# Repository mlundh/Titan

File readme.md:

# Titan

Development board for robotics, drones and misc. projects. Initially designed to support [QuadSys](https://github.com/mlundh/QuadSys) development.

## Getting Started

These instructions will get you a copy of the project up and running on your local machine for development.

### Prerequisites

Install [KiCad](https://kicad-pcb.org/download/)

Example KiCad 5.1 for ubuntu:
```
sudo add-apt-repository --yes ppa:js-reynaud/kicad-5.1
sudo apt update
sudo apt install --install-recommends kicad
# If you want demo projects
sudo apt install kicad-demo
```
## Versioning

Each version I have manufactured is listed as a tag with only a version number in the repository.

Example:
```
v1.0
```
Each version that has been manufactured and verified will get tagged with vesion number and "_verified".

Example (does at time of writing this not exist):
```
v1.0_verified
```

## Authors

* **Martin Lundh** - [mlundh](https://github.com/mlundh)

## License

This project is licensed under the MIT License - see the [LICENSE.md](LICENSE.md) file for details

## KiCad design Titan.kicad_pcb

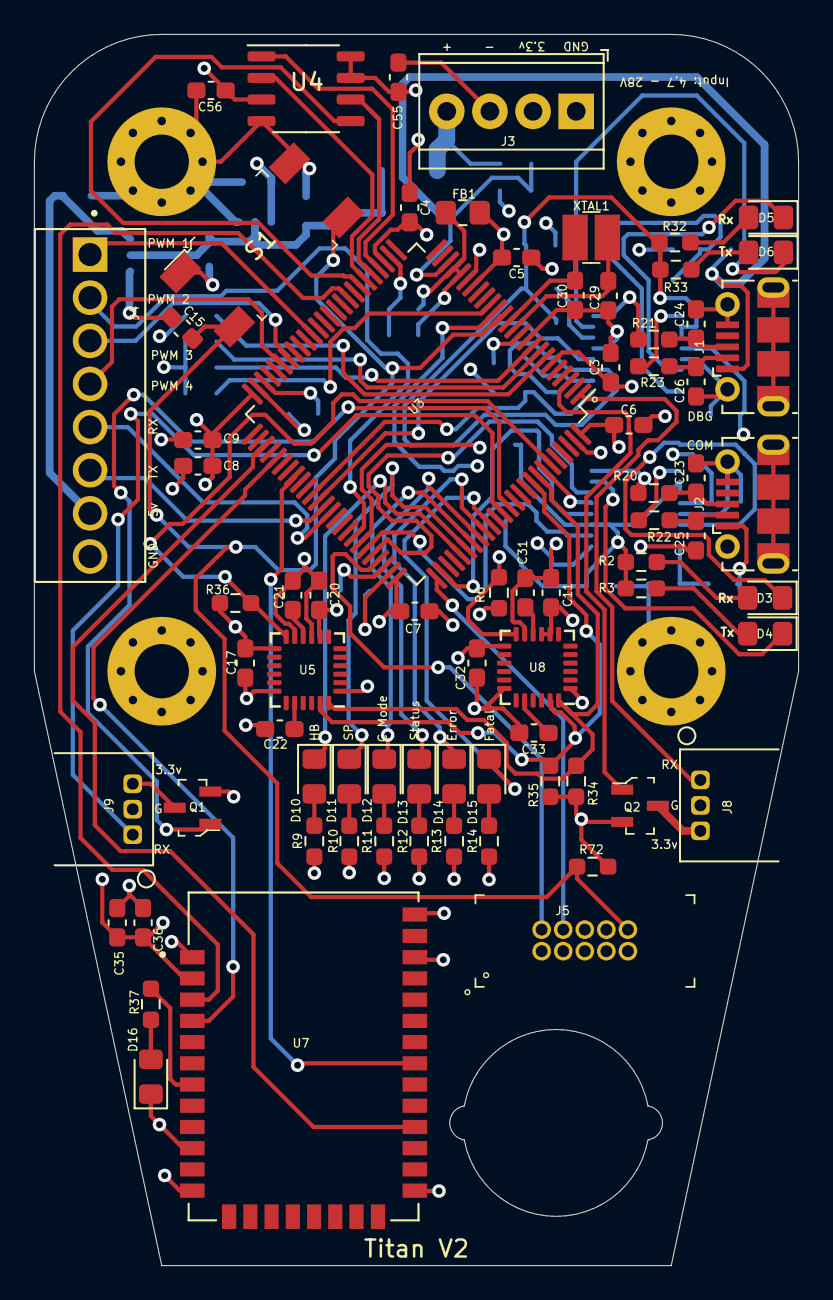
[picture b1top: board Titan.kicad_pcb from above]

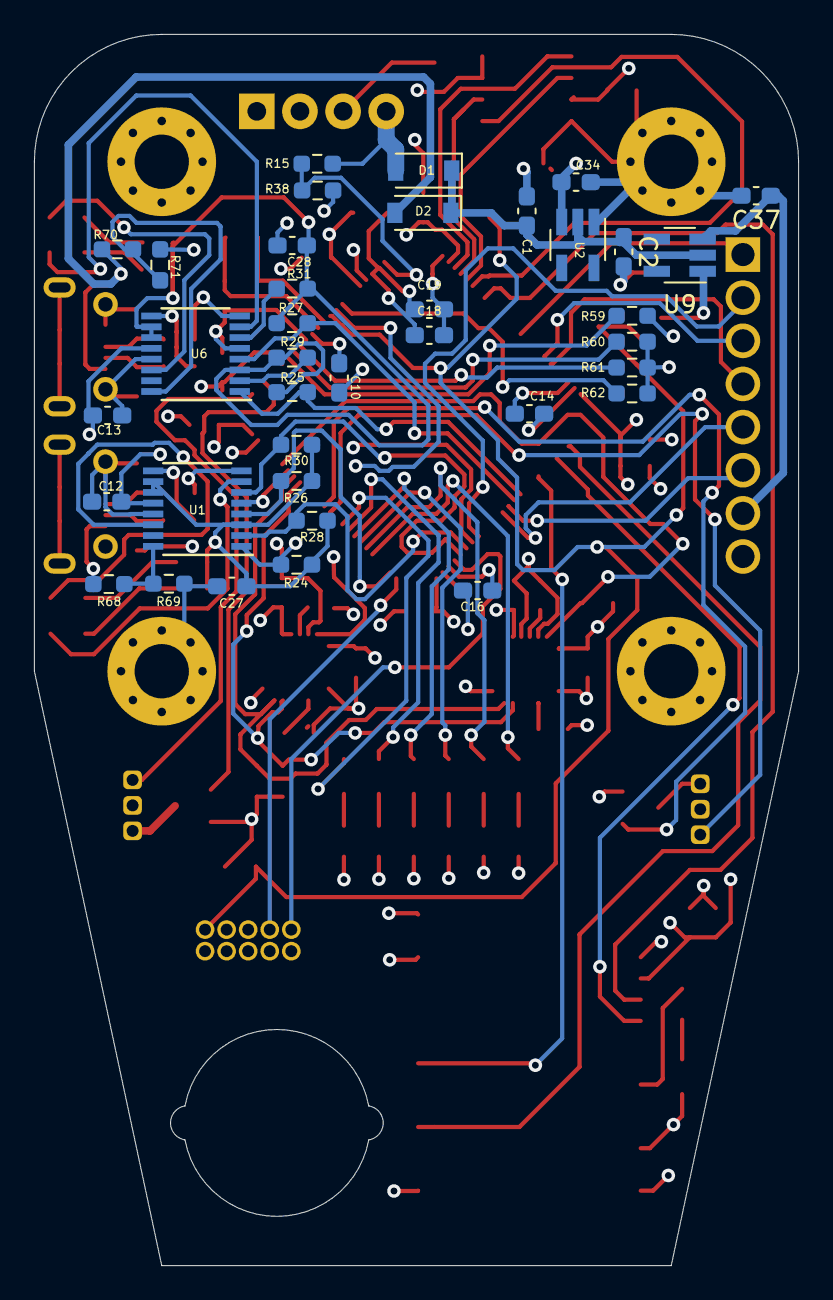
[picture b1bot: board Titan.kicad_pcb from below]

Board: 4 copper layers, 45.0 x 72.5 mm, 115 parts (37 on the bottom side), 90 nets.

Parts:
C1, C2, C14, C16, C22, C33, C34, C37: 2.2uF; C_0603_1608Metric_Pad1.08x0.95mm_HandSolder
C3, C4, C5, C6, C7, C8, C9, C12, C13, C15, C18, C27, C28: 100nF; C_0603_1608Metric_Pad1.08x0.95mm_HandSolder
C10: 10uF; C_0603_1608Metric_Pad1.08x0.95mm_HandSolder
C11, C20, C21, C31, C55: 0.1uF; C_0603_1608Metric_Pad1.08x0.95mm_HandSolder
C17, C32, C56: 10nF; C_0603_1608Metric_Pad1.08x0.95mm_HandSolder
C19, C35: 1uF; C_0603_1608Metric_Pad1.08x0.95mm_HandSolder
C23, C24, C25, C26: 47pF; C_0603_1608Metric_Pad1.08x0.95mm_HandSolder
C29, C30, C36: 8.2pF; C_0603_1608Metric_Pad1.08x0.95mm_HandSolder
D1, D2: D_Schottky; D_SOD-123
D3, D5: RXLED; LED_0805_2012Metric_Pad1.15x1.40mm_HandSolder
D4, D6: TXLED; LED_0805_2012Metric_Pad1.15x1.40mm_HandSolder
D10: LED_Heartbeat; LED_0805_2012Metric_Pad1.15x1.40mm_HandSolder
D11: LED_Valid_SP; LED_0805_2012Metric_Pad1.15x1.40mm_HandSolder
D12: LED_Status; LED_0805_2012Metric_Pad1.15x1.40mm_HandSolder
D13: LED_Mode; LED_0805_2012Metric_Pad1.15x1.40mm_HandSolder
D14: LED_Error_Log; LED_0805_2012Metric_Pad1.15x1.40mm_HandSolder
D15: LED_Fatal_Error; LED_0805_2012Metric_Pad1.15x1.40mm_HandSolder
D16: LED; LED_0805_2012Metric_Pad1.15x1.40mm_HandSolder
FB1: Ferrite_Bead; R_0805_2012Metric_Pad1.20x1.40mm_HandSolder
H1, H2, H3, H4: MountingHole_Pad; MountingHole_3.2mm_M3_Pad_Via
J1, J2: USB_B_Micro; USB_Micro-B_Molex-105017-0001
J3: PWR CON; TerminalBlock_TE_282834-4_1x04_P2.54mm_Horizontal
J4: Screw_Terminal_01x08; HDRV8W85P254_8X1_2078X650X1000
J5: Debug; PinHeader_2x5_P1.27mm_Drill.7mm
J8, J9: S3B-ZR(LF)(SN)
Q1, Q2: NDS332P; SOT-23-3
R2, R3, R9, R10, R11, R12, R13, R14, R32, R33, R37: 330; R_0603_1608Metric_Pad0.98x0.95mm_HandSolder
R6, R36: 47k; R_0603_1608Metric_Pad0.98x0.95mm_HandSolder
R15: 100k; R_0603_1608Metric_Pad0.98x0.95mm_HandSolder
R20, R21, R22, R23: 27; R_0603_1608Metric_Pad0.98x0.95mm_HandSolder
R24, R25, R26, R27, R28, R29, R30, R31, R59, R60, R61, R62, R69, R71, R72: 10k; R_0603_1608Metric_Pad0.98x0.95mm_HandSolder
R34, R35: 4.7k; R_0603_1608Metric_Pad0.98x0.95mm_HandSolder
R38: 20k; R_0603_1608Metric_Pad0.98x0.95mm_HandSolder
R68, R70: 4,7k; R_0603_1608Metric_Pad0.98x0.95mm_HandSolder
S1: Reset button; Switch_Tactile_SMD_6x6mm
U1, U6: FT230XS; SSOP-16_3.9x4.9mm_P0.635mm
U2: ST732M33R; SOT-23-5_HandSoldering
U3: STM32F413VGTx; LQFP-100_14x14mm_P0.5mm
U4: CY15B104Q; SOP-8_3.9x4.9mm_P1.27mm
U5, U8: MPU-6050; InvenSense_QFN-24_4x4mm_P0.5mm
U7: XBEE3Micro; XCVR_XB3-24Z8UM-J
U9: ST732M50R; SOT-23-5_HandSoldering
XTAL1: NX3225GD-8MHZ-STD-CRA-3; SMD-2_3.2x2.5mm

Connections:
+5V: C37.1, J4.7, U9.3
/ADC_BAT: R15.1, R38.2, U3.23
/I2C_SCL_IMU: R35.2, U3.92, U5.23, U8.23
/I2C_SDA_IMU: R34.2, U3.93, U5.24, U8.24
/IMU1_INT: R36.1, U3.95, U5.12
/IMU2_INT: R6.1, U3.15, U8.12
/LED_CTRL_MODE: D12.1, U3.82
/LED_ERROR: D14.1, U3.84
/LED_FATAL: D15.1, U3.85
/LED_HEARTBEAT: D10.1, U3.80
/LED_SETPOINT: D11.1, U3.81
/LED_STATUS: D13.1, U3.83
/PWM_1: J4.1, U3.40
/PWM_2: J4.2, U3.68
/PWM_3: J4.3, U3.44
/PWM_4: J4.4, U3.45
/RC_1_PWR_CTRL: Q2.1, U3.3
/RC_2_PWR_CTRL: Q1.1, U3.88
/REV1: R59.2, U3.7
/REV2: R60.2, U3.8
/REV3: R61.2, U3.9
/REV4: R62.2, U3.16
/SPI_MEM_MISO: U3.31, U4.2
/SPI_MEM_MOSI: U3.32, U4.5
/SPI_MEM_NSS: U3.29, U4.1
/SPI_MEM_SCK: U3.30, U4.6
/SWCLK: J5.4, U3.76
/SWDIO: J5.2, U3.72
/UART_COM_CTS: U3.58, U7.27
/UART_COM_RTS: U3.53, U7.24
/UART_COM_RX: U3.34, U7.3
/UART_COM_TX: U3.55, U7.4
/UART_COM_USB_CTS: R28.2, U1.2, U3.70
/UART_COM_USB_RTS: R30.2, U1.6, U3.71
/UART_COM_USB_RX: R24.2, U1.1, U3.69
/UART_COM_USB_TX: R26.2, U1.4, U3.77
/UART_DBG_RX: R25.2, U3.61, U6.1
/UART_DBG_TX: R27.2, U3.62, U6.4
/UART_MOTOR_2_RX: J4.5, U3.64
/UART_MOTOR_2_TX: J4.6, U3.63
/UART_RC_1_RX: J8.3, U3.1
/UART_RC_2_RX: J9.3, U3.87
/VBUS_COM: D2.2, J1.1, R70.1
/nRESET: C15.1, J5.10, R72.2, S1.3, S1.4, U3.14
GND: C1.2, C2.2, C3.2, C4.2, C5.2, C6.2, C7.2, C8.2, C9.2, C10.2, C11.1, C12.1, C13.1, C14.2, C15.2, C16.2, C17.1, C18.2, C19.2, C20.1, C21.2, C22.2, C23.2, C24.2, C25.2, C26.2, C27.1, C28.1, C29.2, C30.2, C31.2, C32.1, C33.2, C34.2, C35.2, C36.1, C37.2, C55.1, C56.1, D16.1, H1.1, H2.1, H3.1, H4.1, J1.5, J1.6, J2.5, J2.6, J3.1, J3.3, J4.8, J5.3, J5.5, J5.9, J8.2, J9.2, R38.1, R60.1, R61.1, R62.1, R69.2, R71.2, S1.1, S1.2, U1.5, U1.13, U2.1, U3.10, U3.20, U3.27, U3.49, U3.74, U3.94, U3.99, U4.4, U5.1, U5.9, U5.11, U5.18, U6.5, U6.13, U7.1, U7.10, U7.12, U7.21, U7.32, U7.34, U8.1, U8.11, U8.18, U9.1
unnamed: C1.1, C2.1, D1.1, D2.1, U2.2, U9.2
unnamed: C14.1, U3.48
unnamed: C16.1, U3.73
unnamed: C21.1, U5.10
unnamed: C22.1, U5.20
unnamed: C23.1, J2.3, R20.2
unnamed: C24.1, J1.3, R21.2
unnamed: C25.1, J2.2, R22.2
unnamed: C26.1, J1.2, R23.2
unnamed: C27.2, R2.1, R3.1, R24.1, R26.1, R28.1, R30.1, U1.3, U1.10, U1.11
unnamed: C28.2, R25.1, R27.1, R29.1, R31.1, R32.1, R33.1, U6.3, U6.10, U6.11
unnamed: C29.1, U3.12, XTAL1.1
unnamed: C30.1, U3.13, XTAL1.2
unnamed: C31.1, U8.10
unnamed: C33.1, U8.20
unnamed: D1.2, J3.4, R15.2
unnamed: D3.1, U1.14
unnamed: D3.2, R2.2
unnamed: D4.1, U1.7
unnamed: D4.2, R3.2
unnamed: D5.1, U6.14
unnamed: D5.2, R32.2
unnamed: D6.1, U6.7
unnamed: D6.2, R33.2
unnamed: D10.2, R9.2
unnamed: D11.2, R10.2
unnamed: D12.2, R11.2
unnamed: D13.2, R12.2
unnamed: D14.2, R13.2
unnamed: D15.2, R14.2
unnamed: D16.2, R37.2
unnamed: J2.1, R68.1
unnamed: J8.1, Q2.2
unnamed: J9.1, Q1.2
unnamed: R20.1, U1.8
unnamed: R21.1, U6.8
unnamed: R22.1, U1.9
unnamed: R23.1, U6.9
unnamed: R29.2, U6.2
unnamed: R31.2, U6.6
unnamed: R37.1, U7.7
unnamed: R68.2, R69.1, U1.16
unnamed: R70.2, R71.1, U6.16
VDDA_MCU: C18.1, C19.1, FB1.1, U3.21, U3.22
VDD_MCU: C3.1, C4.1, C5.1, C6.1, C7.1, C8.1, C9.1, C10.1, C11.2, C12.2, C13.2, C17.2, C20.2, C32.2, C34.1, C35.1, C36.2, C55.2, C56.2, FB1.2, J3.2, J5.1, Q1.3, Q2.3, R6.2, R9.1, R10.1, R11.1, R12.1, R13.1, R14.1, R34.1, R35.1, R36.2, R59.1, R72.1, U1.12, U2.3, U3.6, U3.11, U3.19, U3.28, U3.50, U3.75, U3.100, U4.3, U4.7, U4.8, U5.8, U5.13, U6.12, U7.2, U8.8, U8.9, U8.13

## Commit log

2020-03-29 Initial version of Titan board.
2020-03-30 Added readme.
2021-02-16 First commit of TitanV2
2021-02-19 As ordered from Aisler.
2021-02-26 Update silkscreen.
2021-03-12 Made the copper pour slightly smaller and removed it around the antenna mount. Also corrected some silkscreen print.
2021-04-04 Added a 5V regulator and connector. This will make it possible to power newer rc receivers.
